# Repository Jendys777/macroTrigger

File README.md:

This is opensource project of a macro keyboard or pad. I call it macroTrigger. As it triggers some macros on your computer.

If you have any questions please read the manual first. Than send me a messagge with question. if you have one.

You can also find the 3D models here: https://www.printables.com/model/1269446-macrotrigger

UPDATE NOTES: 
- V3 firmware helps with the flashing process. Previously, you had to manually reset the device by shorting the RST and GND pins. Now, simply unplug the device, press and hold the encoder, and plug it back in. Keep holding the encoder while starting the flash in your IDE. Once the upload is finished, release the encoder, replug the device, and you are ready to go.

Please DO NOT SHARE, OR SELL THIS PRODCT, without my perrmision. 

contact me on: info@bojler.org

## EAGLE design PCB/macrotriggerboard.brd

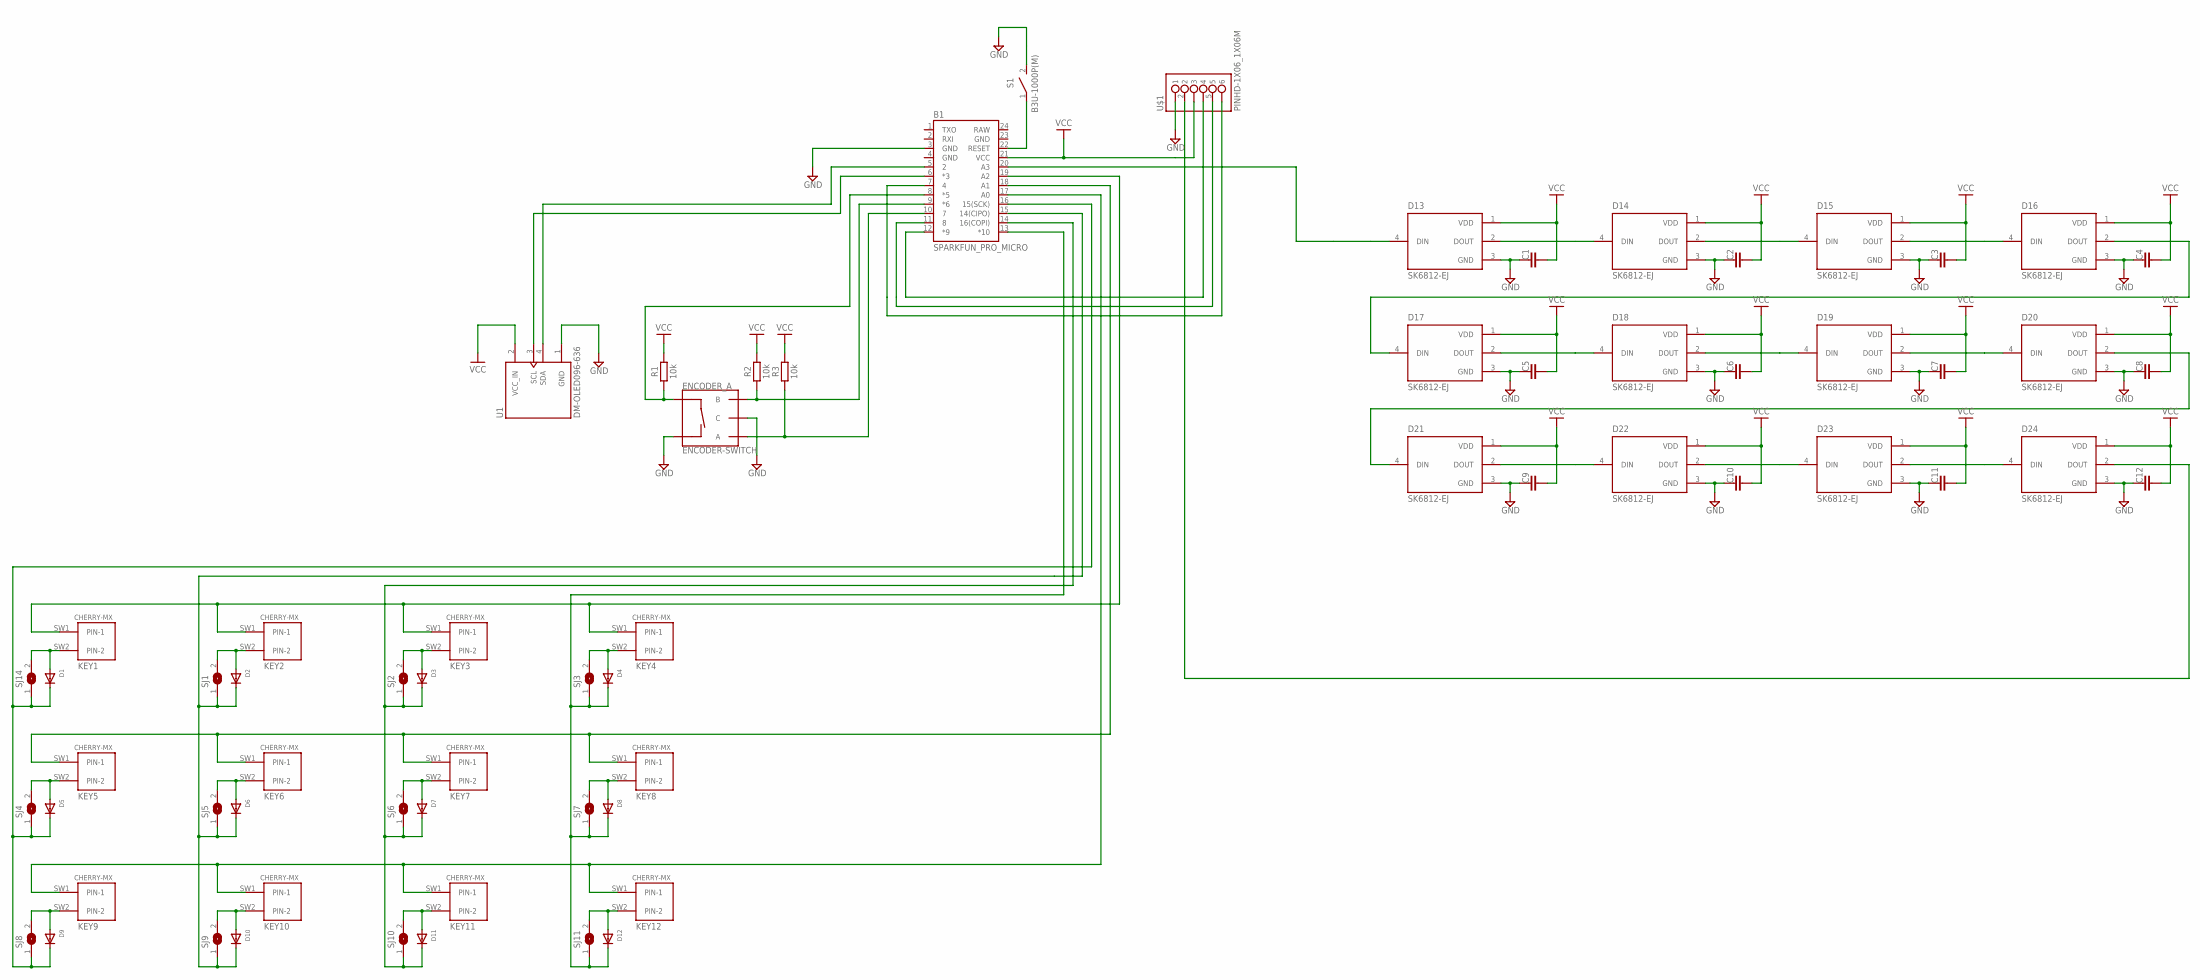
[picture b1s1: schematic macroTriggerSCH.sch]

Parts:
B1: SPARKFUN_PRO_MICRO
C1, C2, C3, C4, C5, C6, C7, C8, C9, C10, C11, C12: C_CHIP-0805(2012-METRIC); CAPC2012X110
D1, D2, D3, D4, D5, D6, D7, D8, D9, D10, D11, D12: DIODESOD-123; SOD-123
D13, D14, D15, D16, D17, D18, D19, D20, D21, D22, D23, D24: SK6812-EJ; LED_SK6812-E
ENCODER_A: ENCODER-SWITCH; ROTARY_ENC_PLAIN
KEY1, KEY2, KEY3, KEY4, KEY5, KEY6, KEY7, KEY8, KEY9, KEY10, KEY11, KEY12: CHERRY-MX
R1, R2, R3: 10k; RESC3216X70
S1: B3U-1000P(M)
SJ1, SJ2, SJ3, SJ4, SJ5, SJ6, SJ7, SJ8, SJ9, SJ10, SJ11, SJ14: SJ
U1: DM-OLED096-636; MODULE_DM-OLED096-636
U$1: PINHD-1X06_1X06M; 1X06

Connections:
GND: B1.3 (GND), B1.4 (GND), B1.23 (GND), C1.1, C2.1, C3.1, C4.1, C5.1, C6.1, C7.1, C8.1, C9.1, C10.1, C11.1, C12.1, D13.3 (GND), D14.3 (GND), D15.3 (GND), D16.3 (GND), D17.3 (GND), D18.3 (GND), D19.3 (GND), D20.3 (GND), D21.3 (GND), D22.3 (GND), D23.3 (GND), D24.3 (GND), ENCODER_A.C, ENCODER_A.SW-, S1.2, U1.1 (GND), U$1.1
unnamed: B1.22 (RESET), S1.1
unnamed: D1.A, KEY1.SW2 (PIN-2), SJ14.2
unnamed: D2.A, KEY2.SW2 (PIN-2), SJ1.2
unnamed: B1.15 (14(CIPO)), D2.C, D6.C, D10.C, SJ1.1, SJ5.1, SJ9.1
unnamed: D24.2 (DOUT), U$1.2
unnamed: B1.10 (7), ENCODER_A.A, R3.1
unnamed: D3.A, KEY3.SW2 (PIN-2), SJ2.2
unnamed: B1.19 (A2), KEY1.SW1 (PIN-1), KEY2.SW1 (PIN-1), KEY3.SW1 (PIN-1), KEY4.SW1 (PIN-1)
unnamed: D13.2 (DOUT), D14.4 (DIN)
unnamed: D4.A, KEY4.SW2 (PIN-2), SJ3.2
unnamed: B1.20 (A3), D13.4 (DIN)
unnamed: D5.A, KEY5.SW2 (PIN-2), SJ4.2
unnamed: D6.A, KEY6.SW2 (PIN-2), SJ5.2
unnamed: B1.13 (*10), D4.C, D8.C, D12.C, SJ3.1, SJ7.1, SJ11.1
unnamed: D7.A, KEY7.SW2 (PIN-2), SJ6.2
unnamed: D8.A, KEY8.SW2 (PIN-2), SJ7.2
unnamed: D9.A, KEY9.SW2 (PIN-2), SJ8.2
unnamed: D10.A, KEY10.SW2 (PIN-2), SJ9.2
unnamed: B1.14 (16(COPI)), D3.C, D7.C, D11.C, SJ2.1, SJ6.1, SJ10.1
unnamed: D11.A, KEY11.SW2 (PIN-2), SJ10.2
unnamed: D12.A, KEY12.SW2 (PIN-2), SJ11.2
unnamed: B1.11 (8), U$1.5
unnamed: B1.12 (*9), U$1.4
unnamed: B1.7 (4), U$1.6
unnamed: D14.2 (DOUT), D15.4 (DIN)
unnamed: D15.2 (DOUT), D16.4 (DIN)
unnamed: B1.18 (A1), KEY5.SW1 (PIN-1), KEY6.SW1 (PIN-1), KEY7.SW1 (PIN-1), KEY8.SW1 (PIN-1)
unnamed: B1.9 (*6), ENCODER_A.B, R2.1
unnamed: B1.8 (*5), ENCODER_A.SW+, R1.1
unnamed: B1.5 (2), U1.4 (SDA)
unnamed: B1.6 (*3), U1.3 (SCL)
unnamed: B1.17 (A0), KEY9.SW1 (PIN-1), KEY10.SW1 (PIN-1), KEY11.SW1 (PIN-1), KEY12.SW1 (PIN-1)
unnamed: D16.2 (DOUT), D17.4 (DIN)
unnamed: B1.16 (15(SCK)), D1.C, D5.C, D9.C, SJ4.1, SJ8.1, SJ14.1
unnamed: D17.2 (DOUT), D18.4 (DIN)
unnamed: D18.2 (DOUT), D19.4 (DIN)
unnamed: D19.2 (DOUT), D20.4 (DIN)
unnamed: D20.2 (DOUT), D21.4 (DIN)
unnamed: D21.2 (DOUT), D22.4 (DIN)
unnamed: D22.2 (DOUT), D23.4 (DIN)
unnamed: D23.2 (DOUT), D24.4 (DIN)
RAW: B1.24 (RAW)
VCC: B1.21 (VCC), C1.2, C2.2, C3.2, C4.2, C5.2, C6.2, C7.2, C8.2, C9.2, C10.2, C11.2, C12.2, D13.1 (VDD), D14.1 (VDD), D15.1 (VDD), D16.1 (VDD), D17.1 (VDD), D18.1 (VDD), D19.1 (VDD), D20.1 (VDD), D21.1 (VDD), D22.1 (VDD), D23.1 (VDD), D24.1 (VDD), R1.2, R2.2, R3.2, U1.2 (VCC_IN), U$1.3

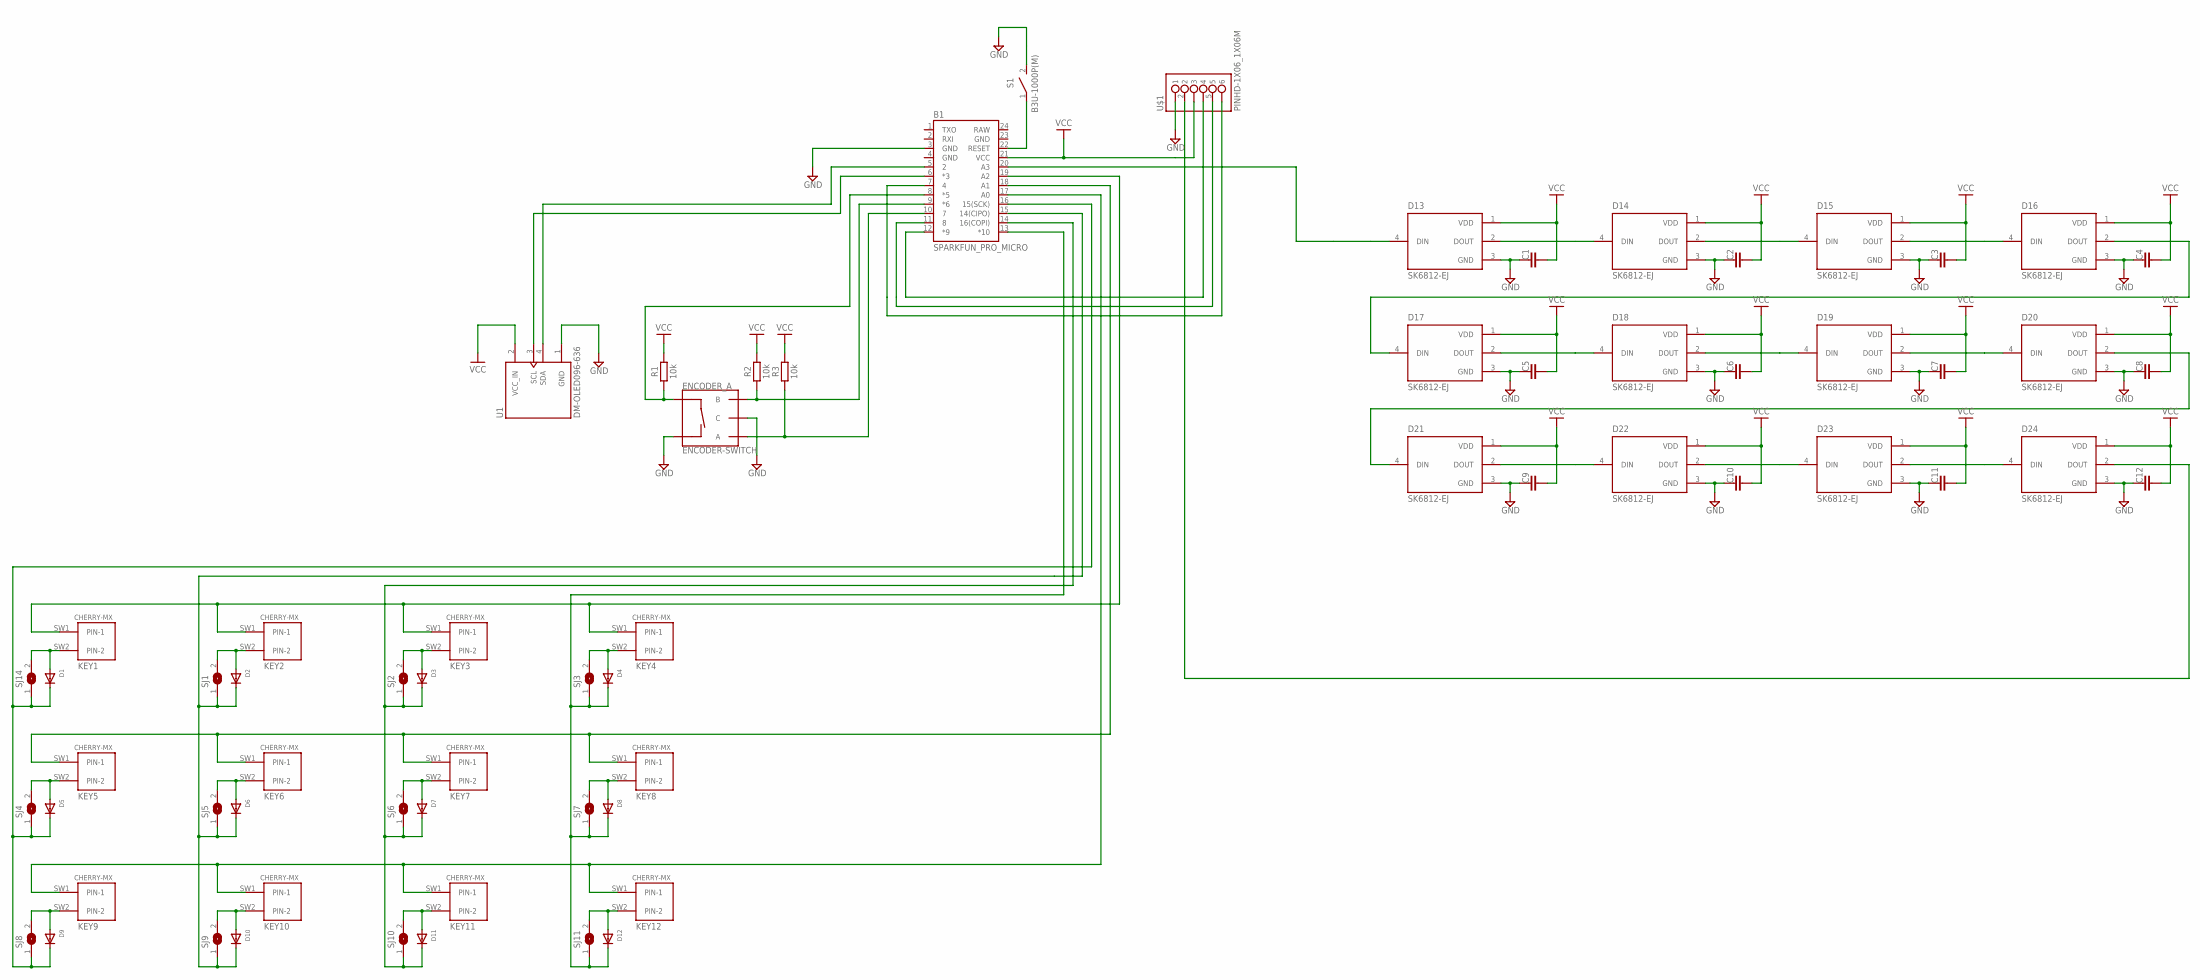
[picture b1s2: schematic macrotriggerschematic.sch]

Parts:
B1: SPARKFUN_PRO_MICRO
C1, C2, C3, C4, C5, C6, C7, C8, C9, C10, C11, C12: C_CHIP-0805(2012-METRIC); CAPC2012X110
D1, D2, D3, D4, D5, D6, D7, D8, D9, D10, D11, D12: DIODESOD-123; SOD-123
D13, D14, D15, D16, D17, D18, D19, D20, D21, D22, D23, D24: SK6812-EJ; LED_SK6812-E
ENCODER_A: ENCODER-SWITCH; ROTARY_ENC_PLAIN
KEY1, KEY2, KEY3, KEY4, KEY5, KEY6, KEY7, KEY8, KEY9, KEY10, KEY11, KEY12: CHERRY-MX
R1, R2, R3: 10k; RESC3216X70
S1: B3U-1000P(M)
SJ1, SJ2, SJ3, SJ4, SJ5, SJ6, SJ7, SJ8, SJ9, SJ10, SJ11, SJ14: SJ
U1: DM-OLED096-636; MODULE_DM-OLED096-636
U$1: PINHD-1X06_1X06M; 1X06

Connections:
GND: B1.3 (GND), B1.4 (GND), B1.23 (GND), C1.1, C2.1, C3.1, C4.1, C5.1, C6.1, C7.1, C8.1, C9.1, C10.1, C11.1, C12.1, D13.3 (GND), D14.3 (GND), D15.3 (GND), D16.3 (GND), D17.3 (GND), D18.3 (GND), D19.3 (GND), D20.3 (GND), D21.3 (GND), D22.3 (GND), D23.3 (GND), D24.3 (GND), ENCODER_A.C, ENCODER_A.SW-, S1.2, U1.1 (GND), U$1.1
unnamed: B1.22 (RESET), S1.1
unnamed: D1.A, KEY1.SW2 (PIN-2), SJ14.2
unnamed: D2.A, KEY2.SW2 (PIN-2), SJ1.2
unnamed: B1.15 (14(CIPO)), D2.C, D6.C, D10.C, SJ1.1, SJ5.1, SJ9.1
unnamed: D24.2 (DOUT), U$1.2
unnamed: B1.10 (7), ENCODER_A.A, R3.1
unnamed: D3.A, KEY3.SW2 (PIN-2), SJ2.2
unnamed: B1.19 (A2), KEY1.SW1 (PIN-1), KEY2.SW1 (PIN-1), KEY3.SW1 (PIN-1), KEY4.SW1 (PIN-1)
unnamed: D13.2 (DOUT), D14.4 (DIN)
unnamed: D4.A, KEY4.SW2 (PIN-2), SJ3.2
unnamed: B1.20 (A3), D13.4 (DIN)
unnamed: D5.A, KEY5.SW2 (PIN-2), SJ4.2
unnamed: D6.A, KEY6.SW2 (PIN-2), SJ5.2
unnamed: B1.13 (*10), D4.C, D8.C, D12.C, SJ3.1, SJ7.1, SJ11.1
unnamed: D7.A, KEY7.SW2 (PIN-2), SJ6.2
unnamed: D8.A, KEY8.SW2 (PIN-2), SJ7.2
unnamed: D9.A, KEY9.SW2 (PIN-2), SJ8.2
unnamed: D10.A, KEY10.SW2 (PIN-2), SJ9.2
unnamed: B1.14 (16(COPI)), D3.C, D7.C, D11.C, SJ2.1, SJ6.1, SJ10.1
unnamed: D11.A, KEY11.SW2 (PIN-2), SJ10.2
unnamed: D12.A, KEY12.SW2 (PIN-2), SJ11.2
unnamed: B1.11 (8), U$1.5
unnamed: B1.12 (*9), U$1.4
unnamed: B1.7 (4), U$1.6
unnamed: D14.2 (DOUT), D15.4 (DIN)
unnamed: D15.2 (DOUT), D16.4 (DIN)
unnamed: B1.18 (A1), KEY5.SW1 (PIN-1), KEY6.SW1 (PIN-1), KEY7.SW1 (PIN-1), KEY8.SW1 (PIN-1)
unnamed: B1.9 (*6), ENCODER_A.B, R2.1
unnamed: B1.8 (*5), ENCODER_A.SW+, R1.1
unnamed: B1.5 (2), U1.4 (SDA)
unnamed: B1.6 (*3), U1.3 (SCL)
unnamed: B1.17 (A0), KEY9.SW1 (PIN-1), KEY10.SW1 (PIN-1), KEY11.SW1 (PIN-1), KEY12.SW1 (PIN-1)
unnamed: D16.2 (DOUT), D17.4 (DIN)
unnamed: B1.16 (15(SCK)), D1.C, D5.C, D9.C, SJ4.1, SJ8.1, SJ14.1
unnamed: D17.2 (DOUT), D18.4 (DIN)
unnamed: D18.2 (DOUT), D19.4 (DIN)
unnamed: D19.2 (DOUT), D20.4 (DIN)
unnamed: D20.2 (DOUT), D21.4 (DIN)
unnamed: D21.2 (DOUT), D22.4 (DIN)
unnamed: D22.2 (DOUT), D23.4 (DIN)
unnamed: D23.2 (DOUT), D24.4 (DIN)
RAW: B1.24 (RAW)
VCC: B1.21 (VCC), C1.2, C2.2, C3.2, C4.2, C5.2, C6.2, C7.2, C8.2, C9.2, C10.2, C11.2, C12.2, D13.1 (VDD), D14.1 (VDD), D15.1 (VDD), D16.1 (VDD), D17.1 (VDD), D18.1 (VDD), D19.1 (VDD), D20.1 (VDD), D21.1 (VDD), D22.1 (VDD), D23.1 (VDD), D24.1 (VDD), R1.2, R2.2, R3.2, U1.2 (VCC_IN), U$1.3

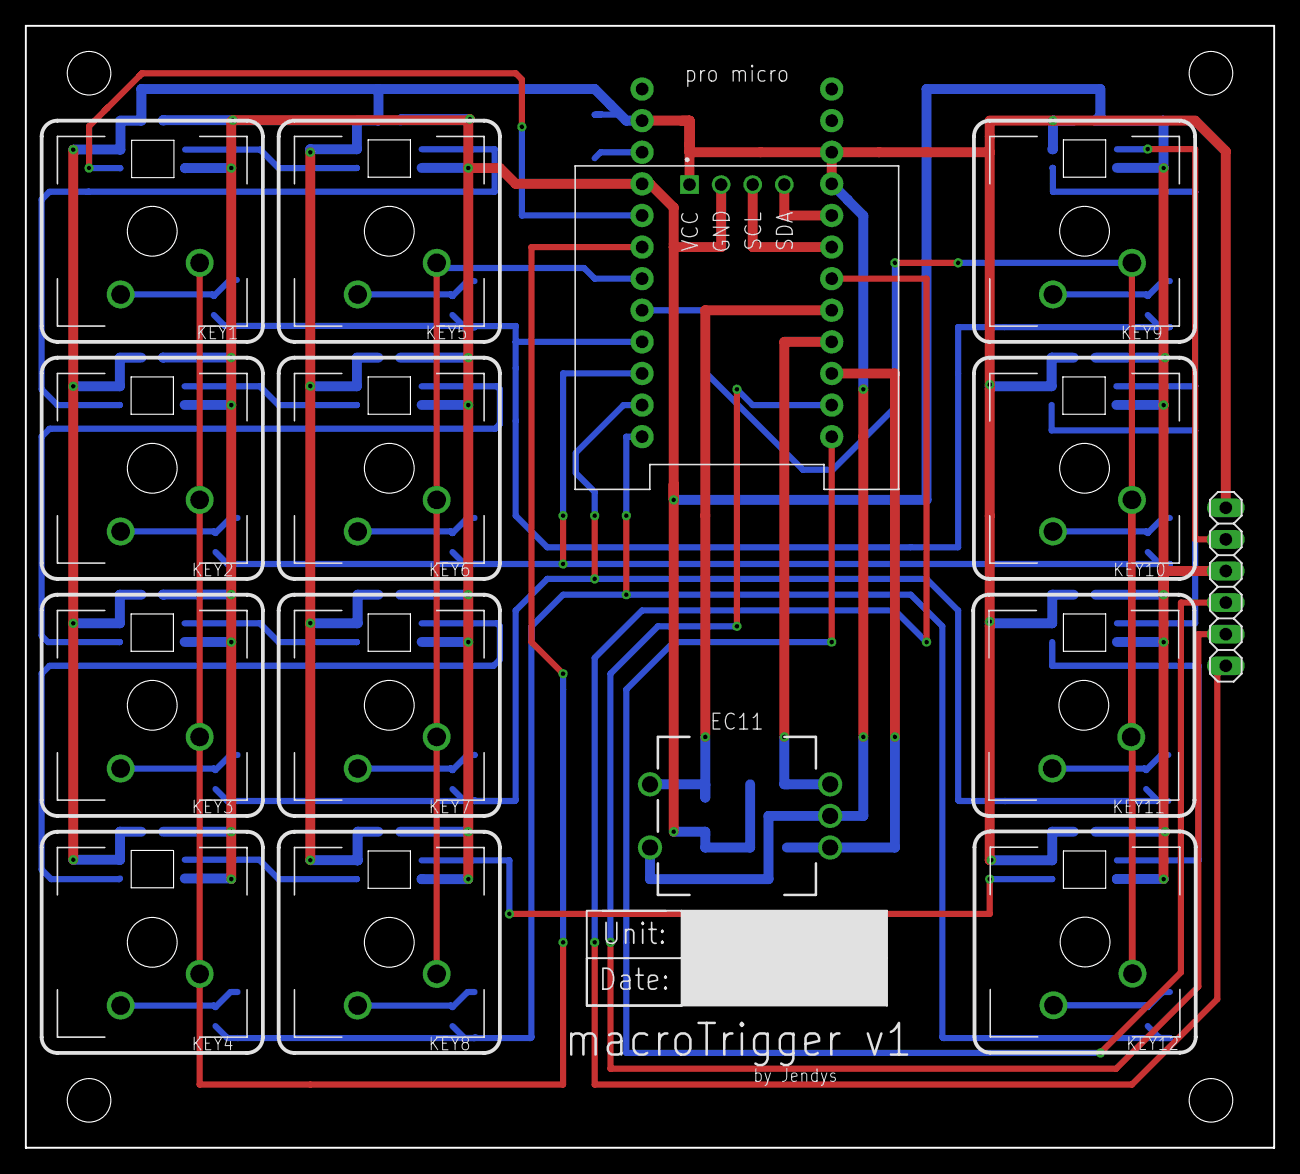
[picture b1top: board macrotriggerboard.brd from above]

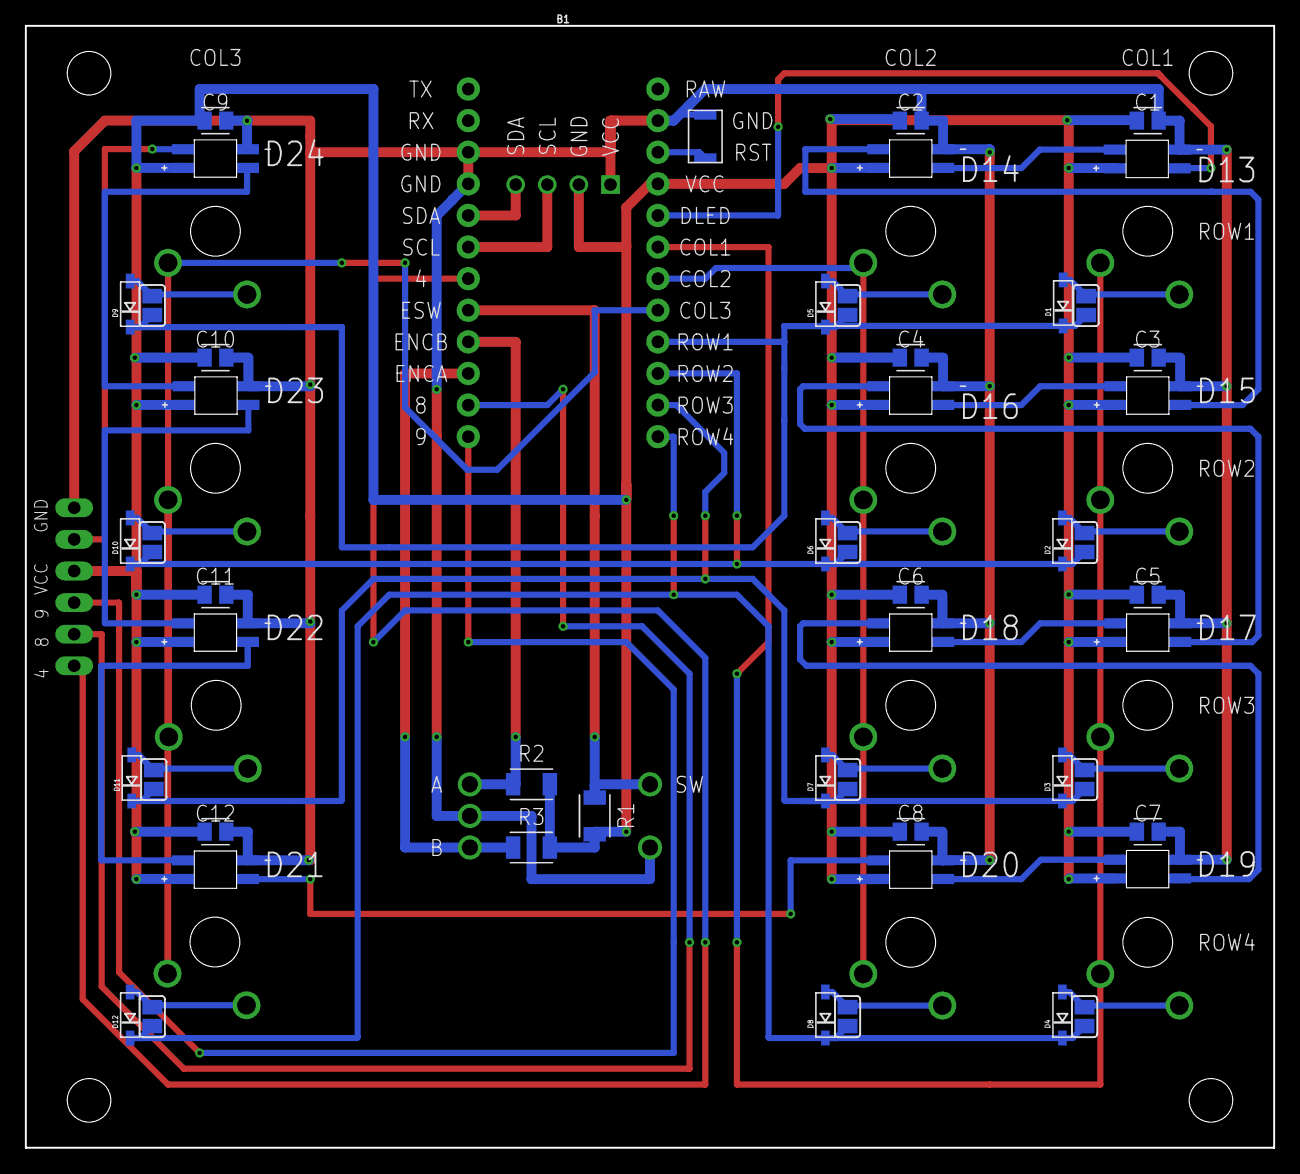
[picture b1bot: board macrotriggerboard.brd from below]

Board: 2 copper layers, 100.3 x 90.2 mm, 68 parts (53 on the bottom side), 43 nets.

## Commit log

2025-04-16 README.md

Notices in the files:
parts and their libraries:
SparkFun-Boards: Licensing: Creative Commons ShareAlike 4.0 International - https://creativecommons.org/licenses/by-sa/4.0
